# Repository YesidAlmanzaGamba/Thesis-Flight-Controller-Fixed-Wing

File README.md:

# Flight Controller and Ground Control Station for a Fixed-Wing UAV

> **Bachelor's thesis (Proyecto de Grado), Electronic Engineering, Universidad de los Andes**
> Author: **Yesid Camilo Almanza Gamba** · Advisor: **Prof. Alba Ávila Bernal**

📄 **[Read the full thesis (PDF, Spanish)](Documento/YesidAlmanza_Tesis_201921773.pdf)** · 🎥 **[Watch the project video](https://youtu.be/uGze4ZMjyZo)**

This project covers the design, build and flight testing of a custom **flight controller for fixed-wing UAVs** based on the **ESP32-S3** (replacing the usual STM32 architecture), along with a **desktop ground control station (GCS)** that shows telemetry in real time and reconstructs the flight path from GPS and altitude data.

## Video

<p align="center">
  
</p>

---

## Features

- **Custom PCB** (KiCad) built around the ESP32-S3 DevKitC-1, with a 3D-printed enclosure.
- **Sensor suite:** BNO055 and MPU6050 IMUs, BMP280 barometer, MS4525 differential-pressure airspeed sensor, NEO-6M GPS and HMC5883L magnetometer.
- **Actuation:** PCA9685 16-channel PWM driver for servos and ESC, driven by a FlySky receiver over iBus/PPM.
- **Telemetry link:** nRF24L01 2.4 GHz radio from the aircraft to a ground receiver.
- **Onboard logging:** flight data is written to a microSD card.
- **Ground control station** (Python + PyQt5): artificial horizon, heading, 3D aircraft model, live plots, a live map (Folium) and data export to JSON/CSV.
- **Post-flight analysis scripts** that produce plots and 2D/3D trajectory maps from logged flights.

## System overview

```
 ┌───────────────── Aircraft ─────────────────┐            ┌──────────── Ground ────────────┐
 │ IMU / Baro / Airspeed / GPS ──► ESP32-S3   │  nRF24L01  │ ESP32-S3 receiver ──USB/serial─┼─► PyQt5 GCS
 │ FlySky RX (iBus/PPM) ──────────►  │        │ ─────────► │  (src/recepcion.cpp)           │   (src/interfazWave)
 │                         PCA9685 ◄─┘──► SD  │            └────────────────────────────────┘
 │                         servos / ESC       │
 └────────────────────────────────────────────┘
```

## Repository layout

| Path | Contents |
|---|---|
| `src/` | Firmware (C++/Arduino, PlatformIO) |
| `src/sensorica/` | Sensor drivers and fusion (IMU, barometer, airspeed, GPS) |
| `src/control/` | Servo / control-surface regulation (`ReguladorServos`) |
| `src/navegacion/` | Control loop and waypoint navigation |
| `src/telemetria/` | FlySky receiver handling |
| `src/utilities/` | OLED display helper |
| `src/main.txt` | **Onboard flight-controller program** (see *Building the firmware*) |
| `src/recepcion.cpp` | **Ground receiver program** (nRF24 → serial / SD) |
| `src/archivosDePrueba/` | Standalone test sketches for individual sensors |
| `src/interfazWave/` | Ground control station (Python / PyQt5) |
| `test/graphs_files/` | Post-flight analysis and plotting scripts |
| `flight_tests/` | Raw flight logs (CSV/JSON), generated plots and HTML maps |
| `PCB/` | KiCad projects (Delta 1.0, Delta 2.0), footprints, symbols, 3D models and fabrication outputs |
| `Documento/` | LaTeX source of the thesis plus the compiled PDF |

## Getting started

### Building the firmware

Requirements: [PlatformIO](https://platformio.org/) (VS Code extension or CLI). Library dependencies are listed in `platformio.ini` and download automatically on the first build.

PlatformIO compiles every `.cpp` file in `src/`, so **only one program with `setup()`/`loop()` can be active at a time**. The inactive ones are stored as `.txt`:

- **Ground receiver** (default): `src/recepcion.cpp` is active.
- **Flight controller:** rename `src/recepcion.cpp` → `recepcion.txt` and `src/main.txt` → `main.cpp`.

```bash
# set upload_port in platformio.ini to your board's port first (COM10 by default)
pio run -t upload
pio device monitor     # 115200 baud
```

### Running the ground control station

Requirements: Python 3.9+.

```bash
cd src/interfazWave
pip install -r requirements.txt
python main.py         # pick the receiver's serial port, then the main window opens
```

> Run it from inside `src/interfazWave/`, because the app loads images and saves data (`datosGuardados/`) through relative paths.

### Analysing flight data

The scripts in `test/graphs_files/` read the CSV logs in `flight_tests/` and generate the plots and Folium maps stored there. They use `pandas`, `matplotlib`, `numpy`, `scipy` and `folium`.

## Thesis document

The thesis (in Spanish, with an English abstract) is in `Documento/`. To rebuild it from source:

```bash
cd Documento
latexmk -pdf main.tex      # uses pdflatex + biber (biblatex)
```

## Results and future work

The controller was integrated into a real fixed-wing aircraft and flown. Orientation, altitude, pressure, temperature and GPS position were sent to the ground station, shown in real time and stored for later analysis. The flight tests showed some data loss and corruption over the nRF24L01 link (mostly altitude and pressure). The proposed next steps are:

- A higher-bandwidth radio together with a protocol such as **MAVLink** for packet integrity.
- A serial buffer in the GCS for smoother real-time display.
- Merging all modules onto a single PCB with improved power regulation and protection.

See chapters *Resultados* and *Conclusiones* of the thesis for details.

## Citation

```bibtex
@thesis{almanza2024flightcontroller,
  author = {Almanza Gamba, Yesid Camilo},
  title  = {Desarrollo e implementación de un controlador de vuelo y estación de control de tierra para un UAV de ala fija},
  school = {Universidad de los Andes},
  type   = {Bachelor's thesis},
  year   = {2024}
}
```

## Acknowledgements

Thanks to Prof. Alba Ávila Bernal for advising this project, and to [@simonpine](https://github.com/simonpine) for contributions to the firmware and the GCS.

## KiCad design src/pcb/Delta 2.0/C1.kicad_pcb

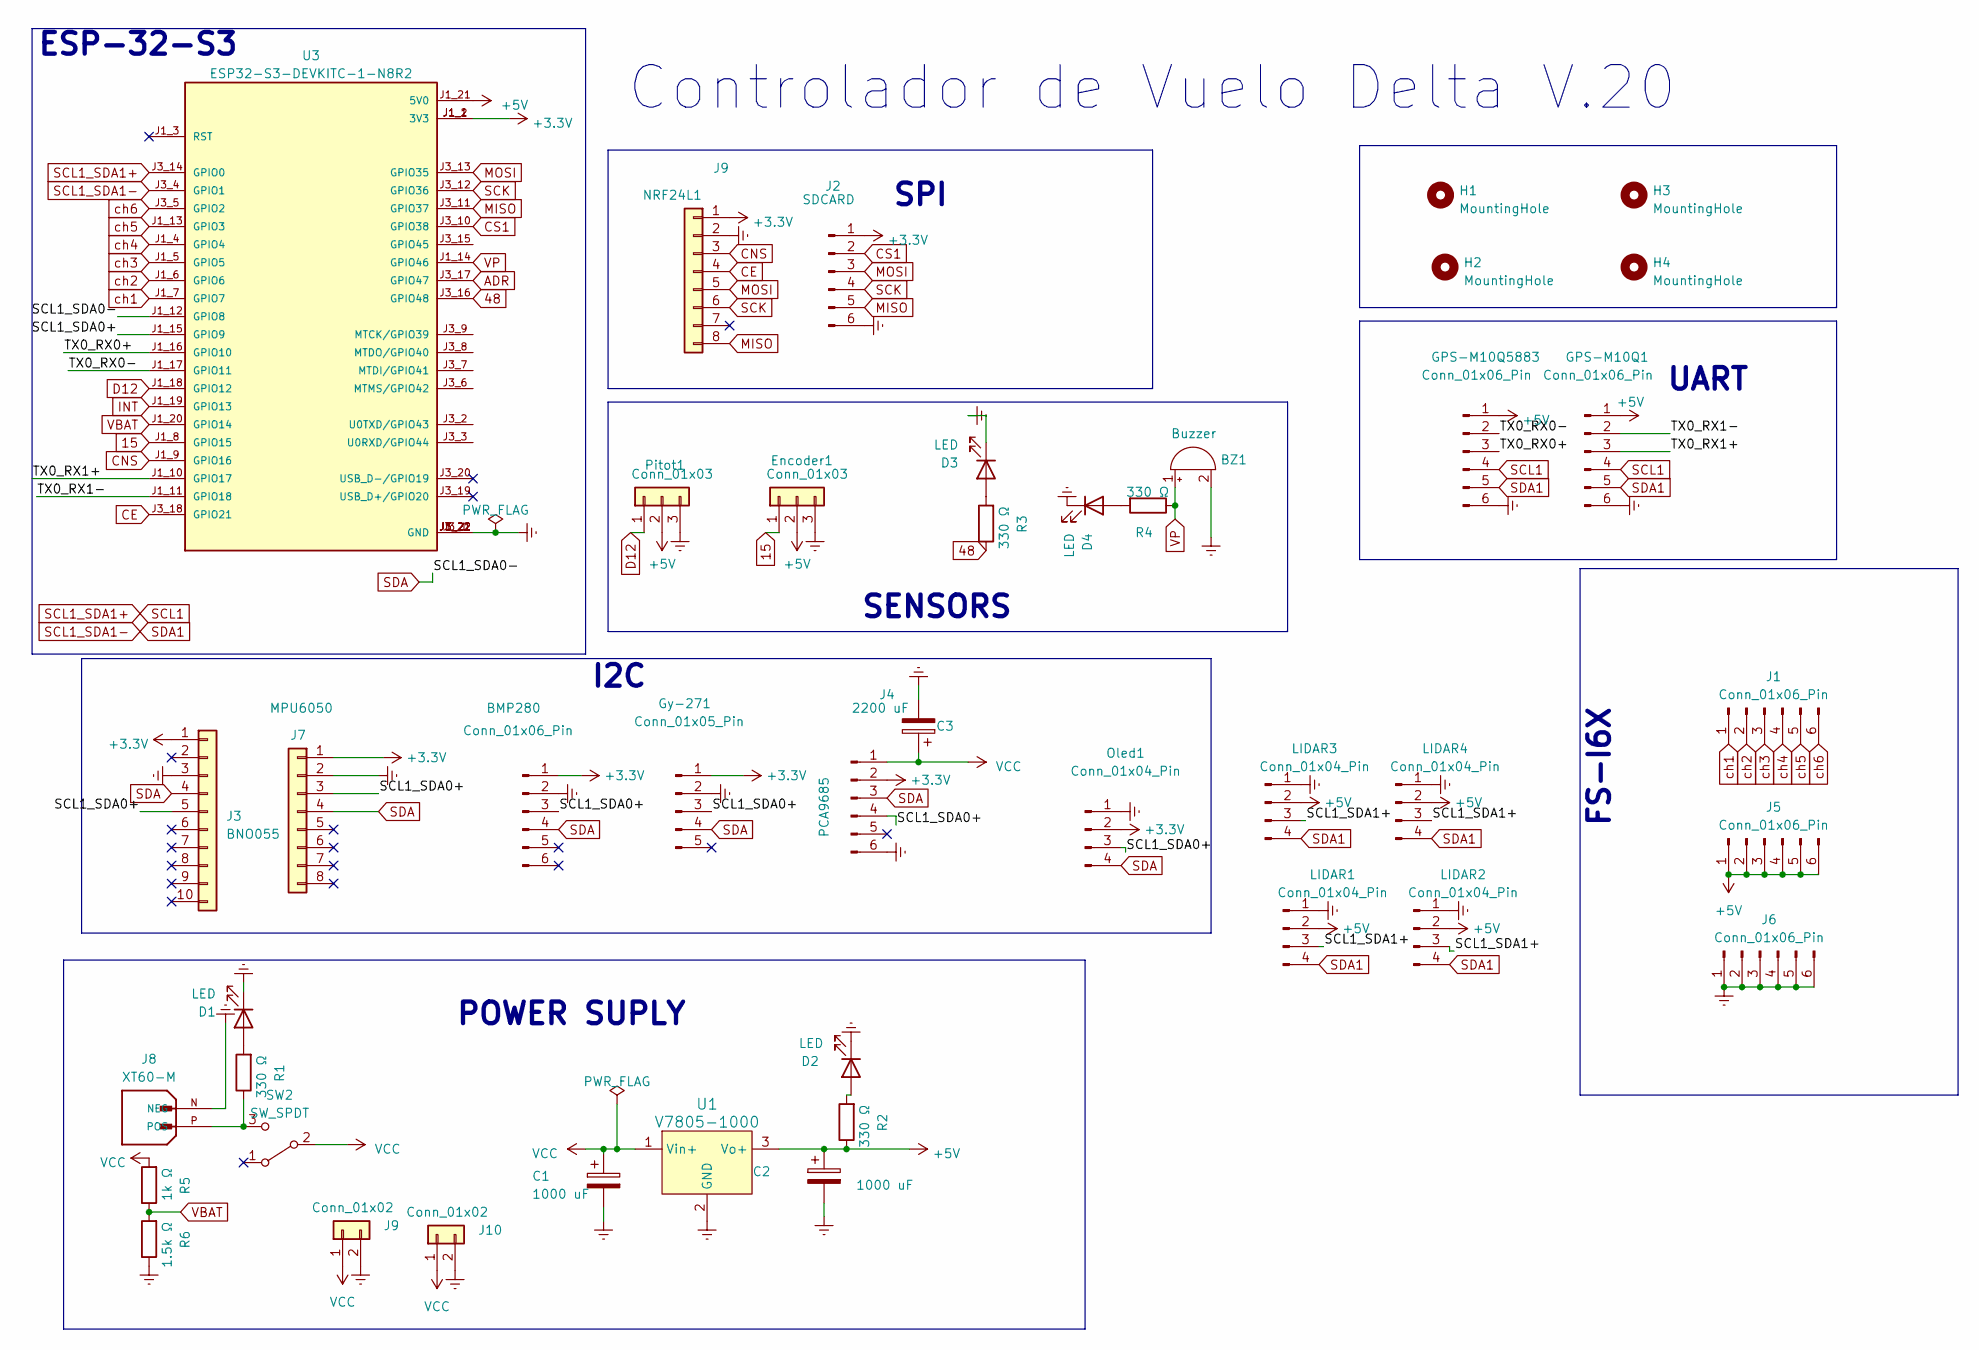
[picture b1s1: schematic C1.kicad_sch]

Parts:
BMP280: Conn_01x06_Pin; module_bme280
BZ1: Buzzer; Buzzer_15x7.5RM7.6
C1, C2: 1000 uF; CP_Elec_10x12.6
C3: 2200 uF; CP_Elec_10x12.6
D1, D2, D3, D4: LED; LED_0402_1005Metric
Encoder1: Conn_01x03; JST_EH_B3B-EH-A_1x03_P2.50mm_Vertical
GPS-M10Q1, GPS-M10Q5883: Conn_01x06_Pin; JST_EH_B6B-EH-A_1x06_P2.50mm_Vertical
Gy-271: Conn_01x05_Pin; Hmc5883l Gy271
H1, H2, H3, H4: MountingHole; MountingHole_3mm_Pad
J1, J5, J6: Conn_01x06_Pin; JST_EH_B6B-EH-A_1x06_P2.50mm_Vertical
J2: SDCARD; PinSocket_1x06_P2.54mm_Vertical
J3: BNO055
J4: PCA9685; PCA 9685
J7: MPU6050; module_mpu6050
J8: XT60-M; AMASS_XT60-M; PARTREV V1.2
J9, J10: Conn_01x02; JST_EH_B2B-EH-A_1x02_P2.50mm_Vertical
LIDAR1, LIDAR2, LIDAR3, LIDAR4: Conn_01x04_Pin; JST_EH_B4B-EH-A_1x04_P2.50mm_Vertical
NRF24L1: J9; PinSocket_2x04_P2.54mm_Vertical
Oled1: Conn_01x04_Pin; OLED
Pitot1: Conn_01x03; JST_EH_B3B-EH-A_1x03_P2.50mm_Vertical
R1, R2: 330 Ω; R_0603_1608Metric
R3, R4: 330 Ω; R_0805_2012Metric
R5: 1k Ω; R_0603_1608Metric
R6: 1.5k Ω; R_0603_1608Metric
SW2: SW_SPDT; Switch_Slide
U1: V7805-1000; 3-SIP_Module_V7805-1000; MPN V7805-1000; Digi-Key_PN 102-1715-ND
U3: ESP32-S3-DEVKITC-1-N8R2; XCVR_ESP32-S3-DEVKITC-1-N8R2; PARTREV V1

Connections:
15: Encoder1.1, U3.J1_8 (GPIO15)
48: R3.1, U3.J3_16 (GPIO48)
+3.3V: BMP280.1, Gy-271.1, J2.1, J3.1, J4.2, J7.1, NRF24L1.1, Oled1.2, U3.J1_1 (3V3), U3.J1_2 (3V3)
+5V: C2.1, Encoder1.2, GPS-M10Q1.1, GPS-M10Q5883.1, J5.1, J5.2, J5.3, J5.4, J5.5, J5.6, LIDAR1.2, LIDAR2.2, LIDAR3.2, LIDAR4.2, Pitot1.2, R2.1, U1.3 (Vo+), U3.J1_21 (5V0)
/SCL1_SDA0+: BMP280.3, Gy-271.3, J3.5, J4.4, J7.3, Oled1.3, U3.J1_15 (GPIO9)
/TX0_RX0+: GPS-M10Q5883.3, U3.J1_16 (GPIO10)
/TX0_RX0-: GPS-M10Q5883.2, U3.J1_17 (GPIO11)
/TX0_RX1+: GPS-M10Q1.3, U3.J1_10 (GPIO17)
/TX0_RX1-: GPS-M10Q1.2, U3.J1_11 (GPIO18)
ADR: U3.J3_17 (GPIO47)
CE: NRF24L1.4, U3.J3_18 (GPIO21)
CNS: NRF24L1.3, U3.J1_9 (GPIO16)
CS1: J2.2, U3.J3_10 (GPIO38)
D12: Pitot1.1, U3.J1_18 (GPIO12)
Earth: BMP280.2, BZ1.2 (+), C1.2, C2.2, C3.2, D1.1 (K), D2.1 (K), D3.1 (K), D4.1 (K), Encoder1.3, GPS-M10Q1.6, GPS-M10Q5883.6, Gy-271.2, J2.6, J3.3, J4.6, J6.1, J6.2, J6.3, J6.4, J6.5, J6.6, J7.2, J8.N (NEG), J9.2, J10.2, LIDAR1.1, LIDAR2.1, LIDAR3.1, LIDAR4.1, NRF24L1.2, Oled1.1, Pitot1.3, R6.1, U1.2 (GND), U3.J1_22 (GND), U3.J3_1 (GND), U3.J3_21 (GND), U3.J3_22 (GND)
INT: U3.J1_19 (GPIO13)
MISO: J2.5, NRF24L1.8, U3.J3_11 (GPIO37)
MOSI: J2.3, NRF24L1.5, U3.J3_13 (GPIO35)
unnamed: D1.2 (A), R1.2
unnamed: D2.2 (A), R2.2
unnamed: D3.2 (A), R3.2
unnamed: D4.2 (A), R4.2
unnamed: J8.P (POS), R1.1, SW2.3 (C)
SCK: J2.4, NRF24L1.6, U3.J3_12 (GPIO36)
SCL1: GPS-M10Q1.4, GPS-M10Q5883.4, LIDAR1.3, LIDAR2.3, LIDAR3.3, LIDAR4.3, U3.J3_14 (GPIO0)
SCL1_SDA1-: GPS-M10Q1.5, GPS-M10Q5883.5, LIDAR1.4, LIDAR2.4, LIDAR3.4, LIDAR4.4, U3.J3_4 (GPIO1)
SDA: BMP280.4, Gy-271.4, J3.4, J4.3, J7.4, Oled1.4, U3.J1_12 (GPIO8)
VBAT: R5.1, R6.2, U3.J1_20 (GPIO14)
VCC: C1.1, C3.1, J4.1, J9.1, J10.1, R5.2, SW2.2 (B), U1.1 (Vin+)
VP: BZ1.1 (-), R4.1, U3.J1_14 (GPIO46)
ch1: J1.1, U3.J1_7 (GPIO7)
ch2: J1.2, U3.J1_6 (GPIO6)
ch3: J1.3, U3.J1_5 (GPIO5)
ch4: J1.4, U3.J1_4 (GPIO4)
ch5: J1.5, U3.J1_13 (GPIO3)
ch6: J1.6, U3.J3_5 (GPIO2)

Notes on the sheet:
I2C
UART
POWER SUPLY
SENSORS
FS-I6X
SPI
Controlador de Vuelo Delta V.20
ESP-32-S3

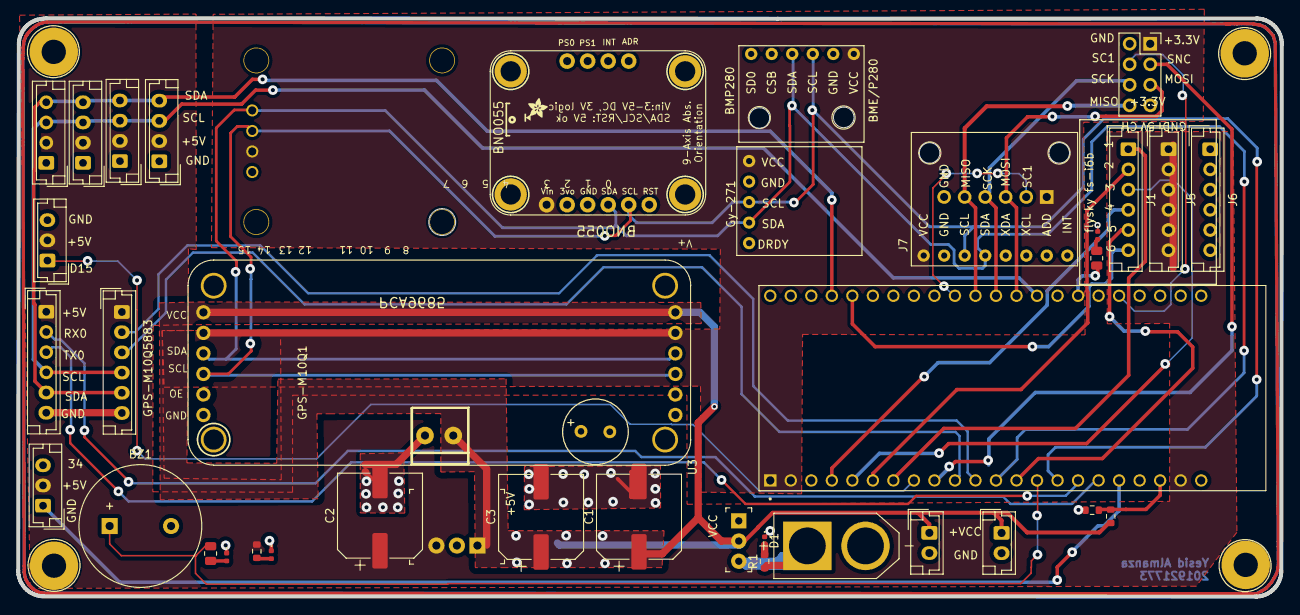
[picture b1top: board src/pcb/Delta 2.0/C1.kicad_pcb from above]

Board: 2 copper layers, 156.4 x 71.6 mm, 43 parts (1 on the bottom side), 34 nets.

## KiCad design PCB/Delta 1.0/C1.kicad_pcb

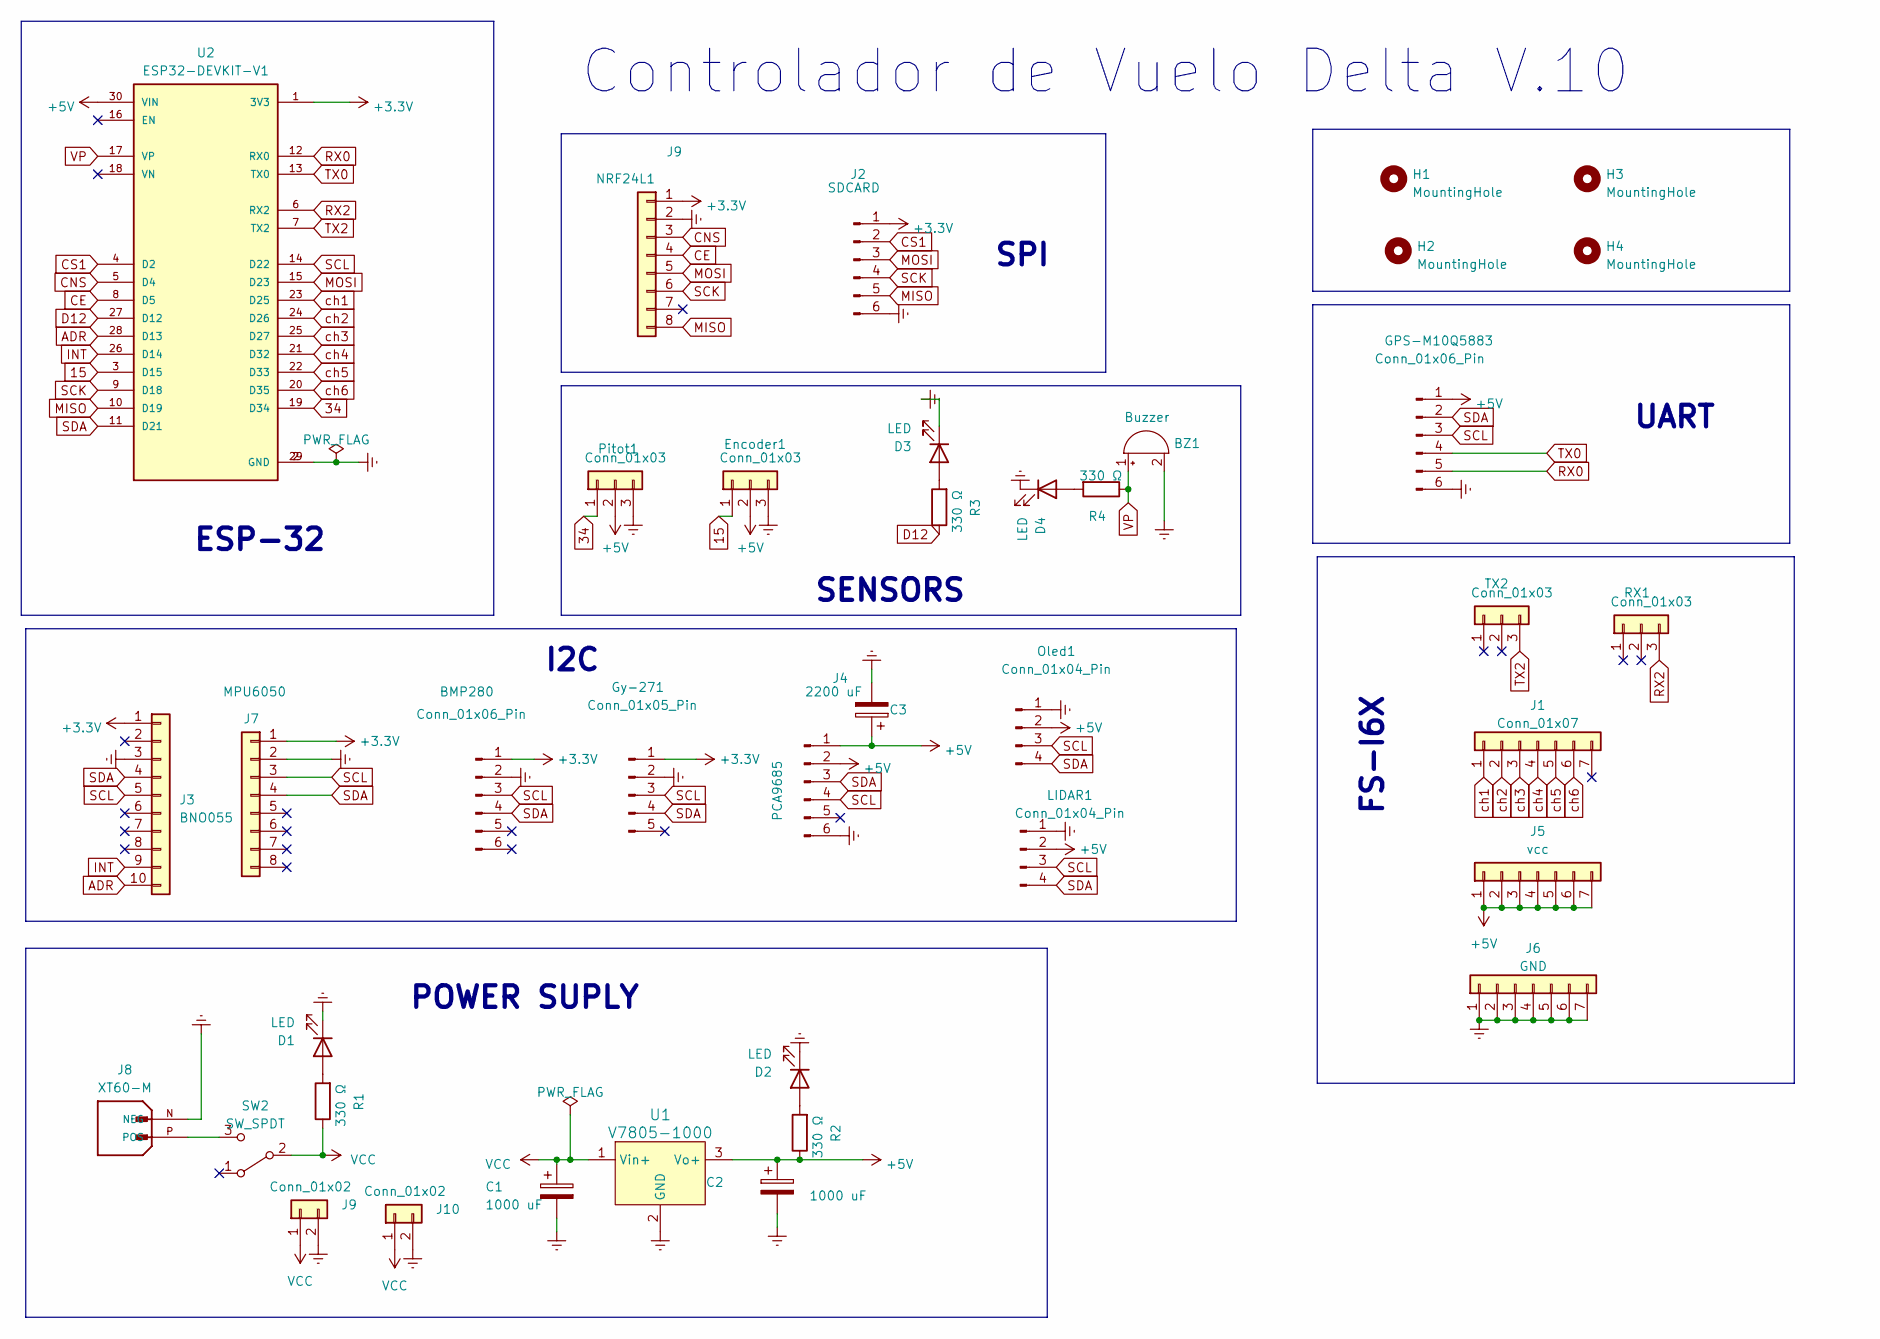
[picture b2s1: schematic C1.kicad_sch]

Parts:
BMP280: Conn_01x06_Pin; module_bme280
BZ1: Buzzer; Buzzer_15x7.5RM7.6
C1, C2: 1000 uF; CP_Radial_D8.0mm_P3.50mm
C3: 2200 uF; CP_Radial_D8.0mm_P3.50mm
D1, D2, D3, D4: LED; LED_1206_3216Metric
Encoder1: Conn_01x03; PinHeader_1x03_P2.54mm_Vertical
GPS-M10Q5883: Conn_01x06_Pin; JST_EH_B6B-EH-A_1x06_P2.50mm_Vertical
Gy-271: Conn_01x05_Pin; Hmc5883l Gy271
H1, H2, H3, H4: MountingHole; MountingHole_3mm_Pad
J1: Conn_01x07; PinHeader_1x07_P2.54mm_Vertical
J2: SDCARD; PinSocket_1x06_P2.54mm_Vertical
J3: BNO055
J4: PCA9685; PCA 9685
J5: vcc; PinHeader_1x07_P2.54mm_Vertical
J6: GND; PinHeader_1x07_P2.54mm_Vertical
J7: MPU6050; module_mpu6050
J8: XT60-M; AMASS_XT60-M; PARTREV V1.2
J9, J10: Conn_01x02; PinSocket_1x02_P2.54mm_Vertical
LIDAR1: Conn_01x04_Pin; JST_EH_B4B-EH-A_1x04_P2.50mm_Vertical
NRF24L1: J9; PinSocket_2x04_P2.54mm_Vertical
Oled1: Conn_01x04_Pin; OLED
Pitot1: Conn_01x03; PinHeader_1x03_P2.54mm_Vertical
R1, R2, R3, R4: 330 Ω; R_0805_2012Metric
RX1: Conn_01x03; PinHeader_1x03_P2.54mm_Vertical
SW2: SW_SPDT; Switch_Slide
TX2: Conn_01x03; PinHeader_1x03_P2.54mm_Vertical
U1: V7805-1000; 3-SIP_Module_V7805-1000; MPN V7805-1000; Digi-Key_PN 102-1715-ND
U2: ESP32-DEVKIT-V1; MODULE_ESP32_DEVKIT_V1; PARTREV N/A

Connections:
15: Encoder1.1, U2.3 (D15)
34: Pitot1.1, U2.19 (D34)
+3.3V: BMP280.1, Gy-271.1, J2.1, J3.1, J7.1, NRF24L1.1, U2.1 (3V3)
+5V: C2.1, C3.1, Encoder1.2, GPS-M10Q5883.1, J4.1, J4.2, J5.1, J5.2, J5.3, J5.4, J5.5, J5.6, J5.7, LIDAR1.2, Oled1.2, Pitot1.2, R2.1, U1.3 (Vo+), U2.30 (VIN)
ADR: J3.10, U2.28 (D13)
CE: NRF24L1.4, U2.8 (D5)
CNS: NRF24L1.3, U2.5 (D4)
CS1: J2.2, U2.4 (D2)
D12: R3.1, U2.27 (D12)
Earth: BMP280.2, BZ1.2 (+), C1.2, C2.2, C3.2, D1.1 (K), D2.1 (K), D3.1 (K), D4.1 (K), Encoder1.3, GPS-M10Q5883.6, Gy-271.2, J2.6, J3.3, J4.6, J6.1, J6.2, J6.3, J6.4, J6.5, J6.6, J6.7, J7.2, J8.N (NEG), J9.2, J10.2, LIDAR1.1, NRF24L1.2, Oled1.1, Pitot1.3, U1.2 (GND), U2.2 (GND), U2.29 (GND)
INT: J3.9, U2.26 (D14)
MISO: J2.5, NRF24L1.8, U2.10 (D19)
MOSI: J2.3, NRF24L1.5, U2.15 (D23)
unnamed: D1.2 (A), R1.2
unnamed: D2.2 (A), R2.2
unnamed: D3.2 (A), R3.2
unnamed: D4.2 (A), R4.2
unnamed: J8.P (POS), SW2.3 (C)
RX0: GPS-M10Q5883.5, U2.12 (RX0)
RX2: RX1.3, U2.6 (RX2)
SCK: J2.4, NRF24L1.6, U2.9 (D18)
SCL: BMP280.3, GPS-M10Q5883.3, Gy-271.3, J3.5, J4.4, J7.3, LIDAR1.3, Oled1.3, U2.14 (D22)
SDA: BMP280.4, GPS-M10Q5883.2, Gy-271.4, J3.4, J4.3, J7.4, LIDAR1.4, Oled1.4, U2.11 (D21)
TX0: GPS-M10Q5883.4, U2.13 (TX0)
TX2: TX2.3, U2.7 (TX2)
VCC: C1.1, J9.1, J10.1, R1.1, SW2.2 (B), U1.1 (Vin+)
VP: BZ1.1 (-), R4.1, U2.17 (VP)
ch1: J1.1, U2.23 (D25)
ch2: J1.2, U2.24 (D26)
ch3: J1.3, U2.25 (D27)
ch4: J1.4, U2.21 (D32)
ch5: J1.5, U2.22 (D33)
ch6: J1.6, U2.20 (D35)

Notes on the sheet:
I2C
UART
POWER SUPLY
SENSORS
FS-I6X
SPI
Controlador de Vuelo Delta V.10
ESP-32

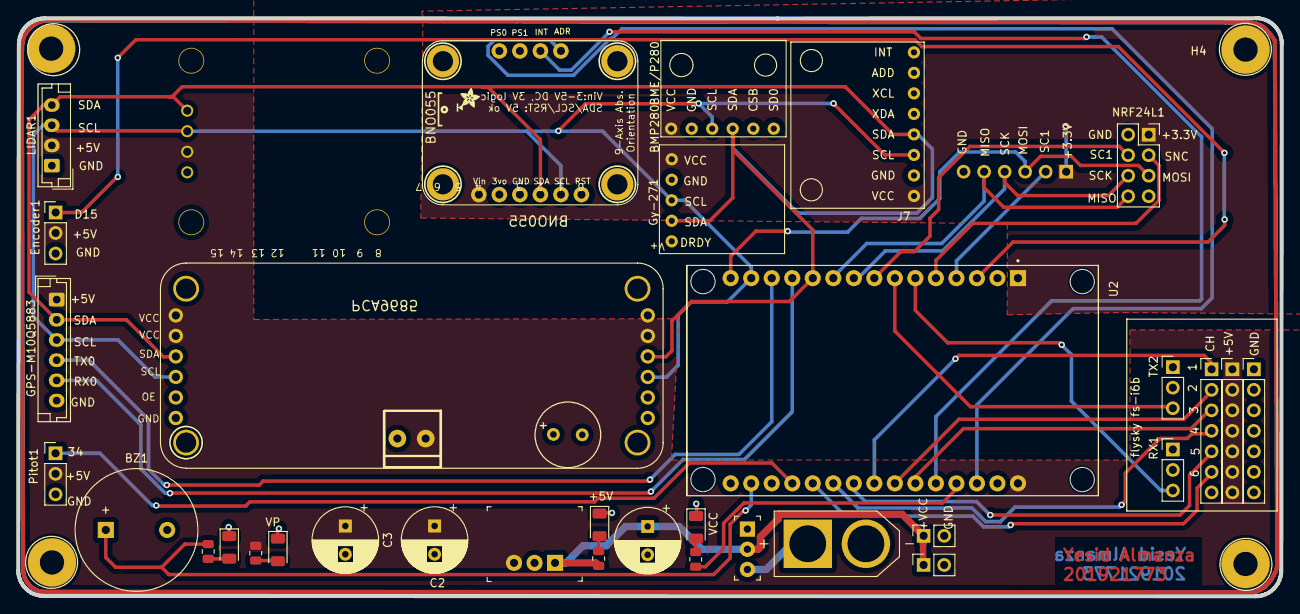
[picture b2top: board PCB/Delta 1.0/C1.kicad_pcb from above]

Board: 2 copper layers, 156.4 x 71.6 mm, 39 parts (1 on the bottom side), 33 nets.

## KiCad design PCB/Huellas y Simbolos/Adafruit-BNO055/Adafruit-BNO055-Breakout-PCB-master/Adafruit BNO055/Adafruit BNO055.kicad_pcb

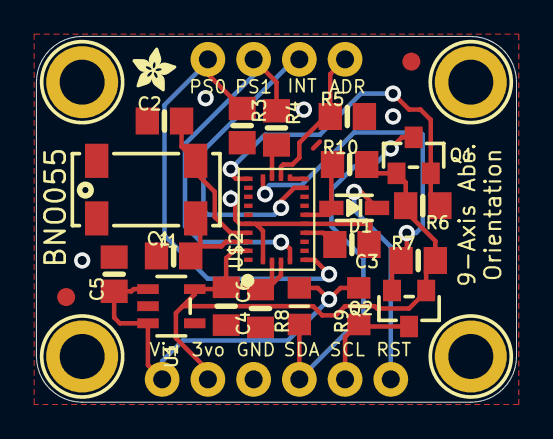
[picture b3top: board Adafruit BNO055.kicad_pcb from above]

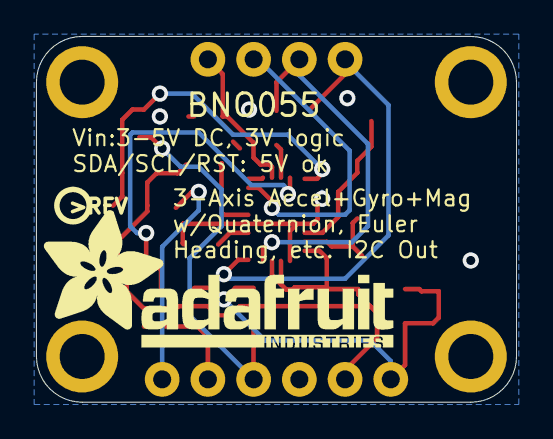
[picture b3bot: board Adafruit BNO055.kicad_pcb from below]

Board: 2 copper layers, 26.7 x 20.3 mm, 31 parts (2 on the bottom side), 16 nets.

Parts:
C1, C2: 22pF; 0805-NO
C3: 0.1uF; 0805-NO
C4: 0.1uF; 0805_10MGAP
C5: 10uF; 0805-NO
C6: 10uF; 0805_10MGAP
D1: 1n4148; SOD-323
FID1, FID2: FIDUCIAL""; FIDUCIAL_1MM
JP1: 1X06_ROUND_76
JP2: 1X04_ROUND_76
Q1, Q2: BSS138; SOT23-WIDE
R3, R4, R5, R6, R7, R10: 10K; 0805-NO
R8, R9: 10K; _0805MP
U1: MIC5225-3.3; SOT23-5
U$2: BNO055
U$3: PCBFEAT-REV-040
U$28: ADAFRUIT_TEXT_20MM
U$29, U$30, U$31, U$32: MOUNTINGHOLE2.5_THICK; MOUNTINGHOLE_2.5_PLATED_THICK
U$33: ADAFRUIT_2.5MM
Y1: 32.768kHz; CRYSTAL_8X3.8

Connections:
3.3V: C4.2, C6.1, JP1.2, Q1.1, Q2.1, R6.2, R7.2, R10.2, U1.5, U$2.3, U$2.4, U$2.28
5.0V: C5.1, JP1.1, R8.2, R9.2, U1.1, U1.3
GND: C1.1, C2.1, C3.1, C4.1, C5.2, C6.2, JP1.3, R3.2, R4.2, R5.2, U1.2, U$2.2, U$2.10, U$2.15, U$2.16, U$2.18, U$2.25
I2CADDR_3V: JP2.4, R5.1, U$2.17
INT_3V: JP2.3, U$2.14
unnamed: C1.2, U$2.27, Y1.P$4
unnamed: C2.2, U$2.26, Y1.P$1
unnamed: C3.2, U$2.9
NRESET_3V: D1.A, R10.1, U$2.11
PS0_3V: JP2.1, R3.1, U$2.6
PS1_3V: JP2.2, R4.1, U$2.5
RST_5V: D1.C, JP1.6
SCL_3V: Q2.2, R7.1, U$2.19
SCL_5V: JP1.5, Q2.3, R9.1
SDA_3V: Q1.2, R6.1, U$2.20
SDA_5V: JP1.4, Q1.3, R8.1

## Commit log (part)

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2024-11-01 Initial Commit , Latex document add
2024-11-01 Document Little Fix
2024-11-05 PCB documents add
2024-11-07 Code For Working Flight Controller and GCS--------------------------------@simonpine
2025-01-14 1 corrección Documento working in Latex
2025-01-15 Correccion latex documento
2025-01-22 Corrección documento
